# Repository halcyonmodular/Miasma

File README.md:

# Miasma
Miasma : Dual VCO Module Documentation

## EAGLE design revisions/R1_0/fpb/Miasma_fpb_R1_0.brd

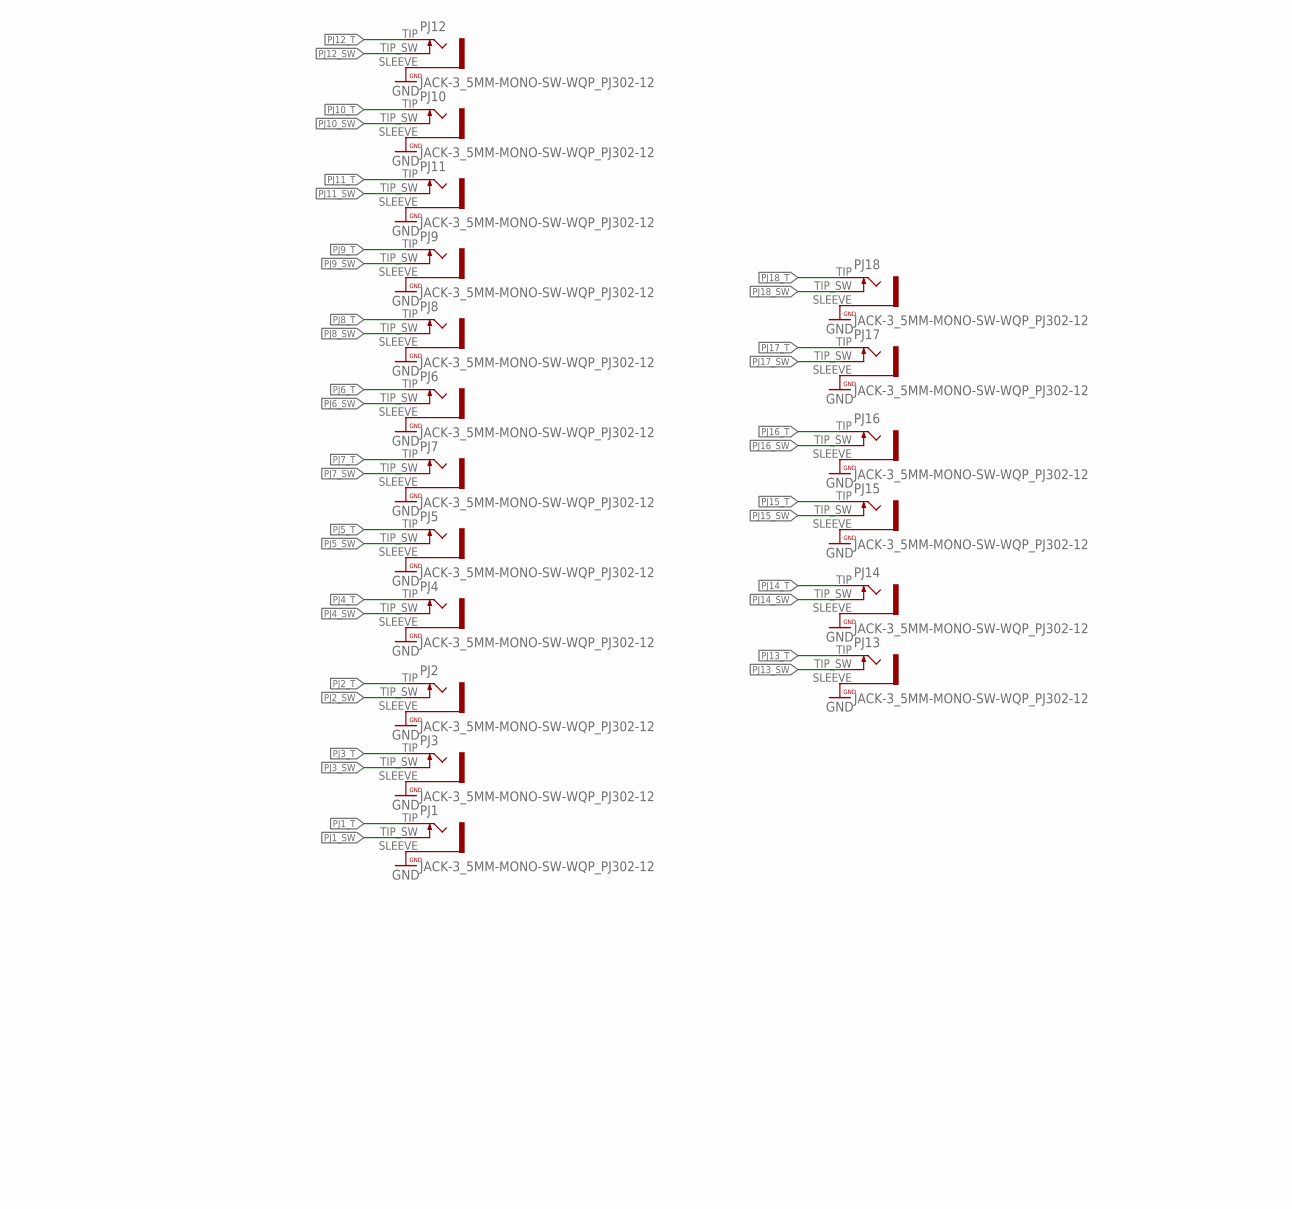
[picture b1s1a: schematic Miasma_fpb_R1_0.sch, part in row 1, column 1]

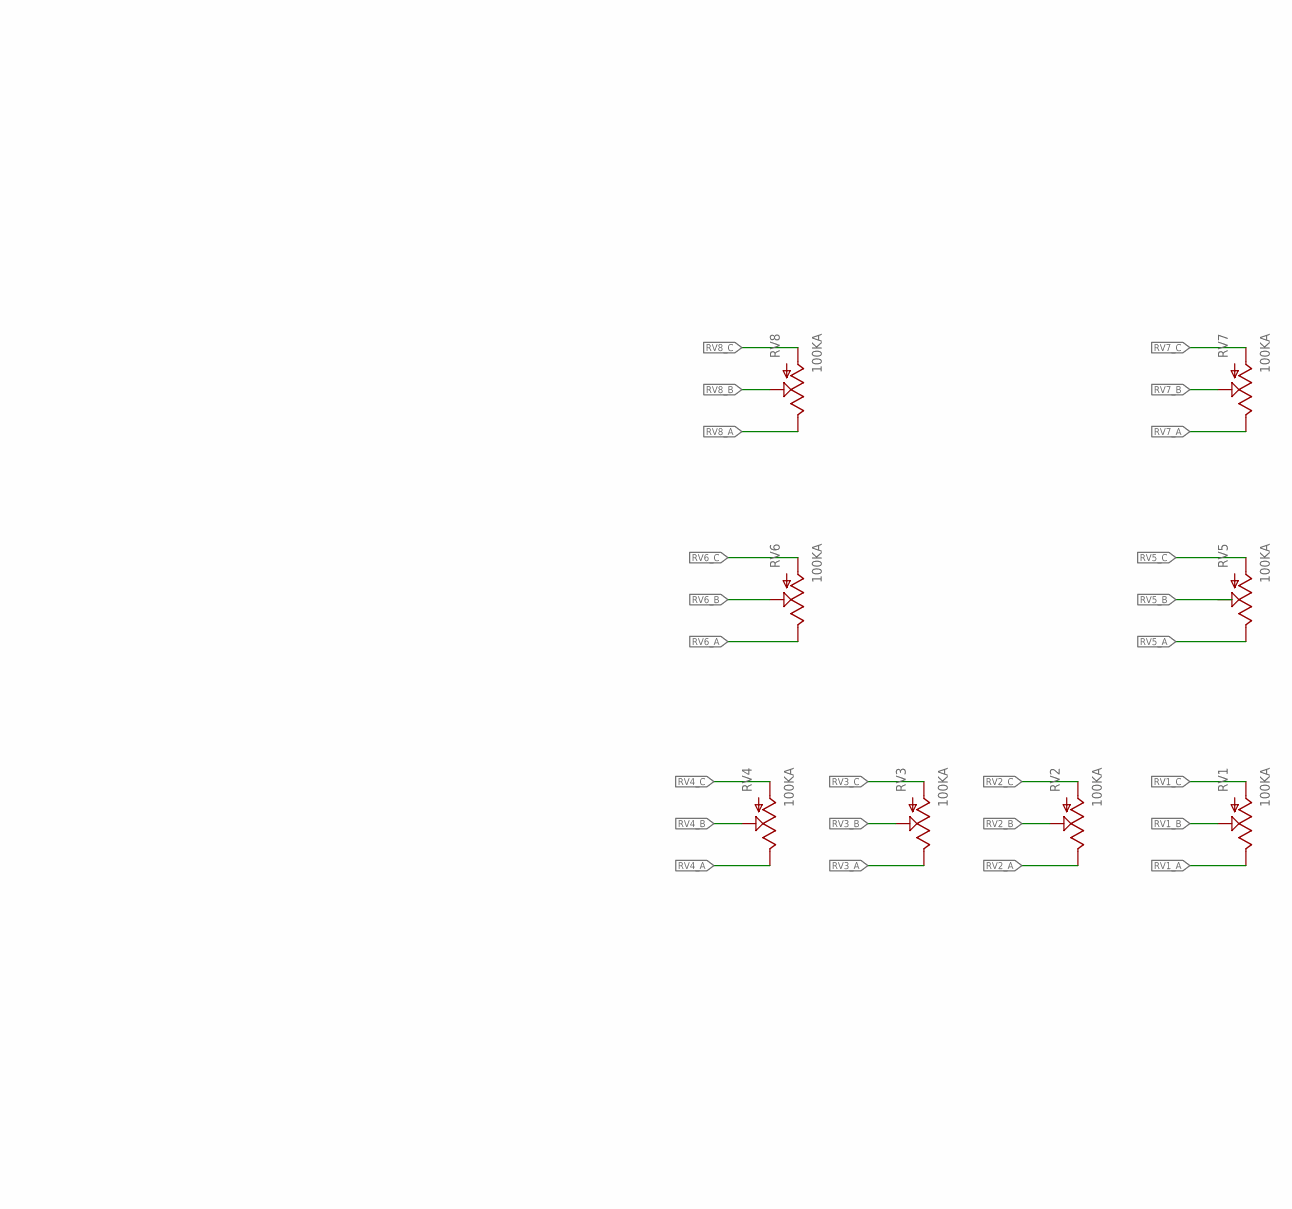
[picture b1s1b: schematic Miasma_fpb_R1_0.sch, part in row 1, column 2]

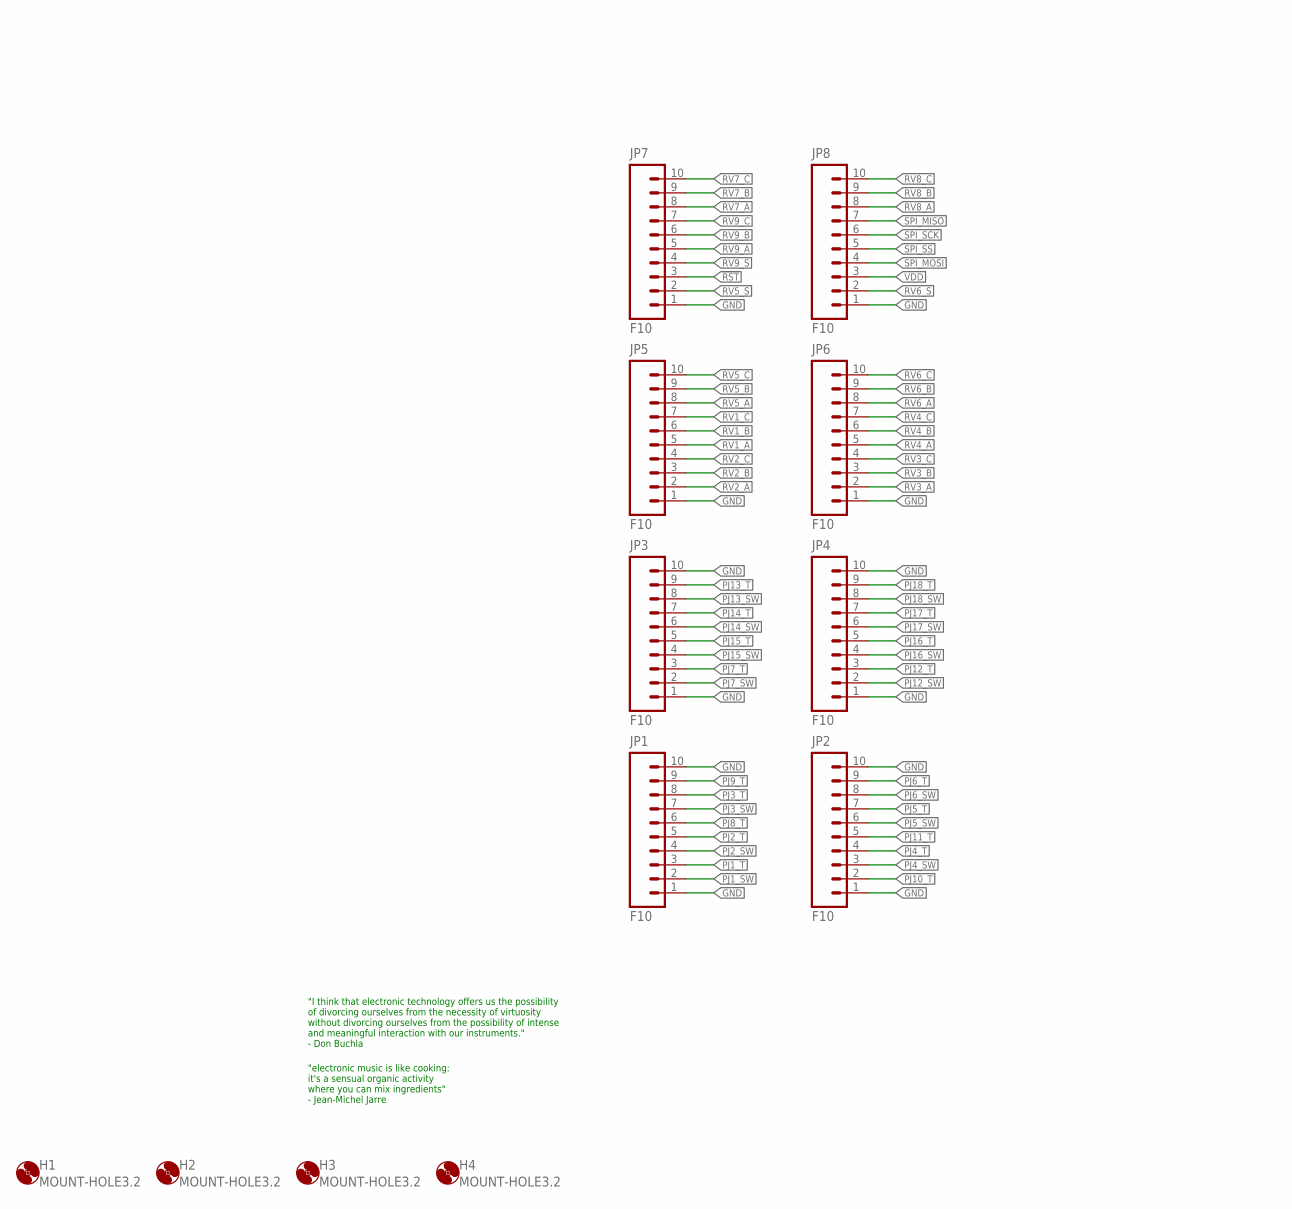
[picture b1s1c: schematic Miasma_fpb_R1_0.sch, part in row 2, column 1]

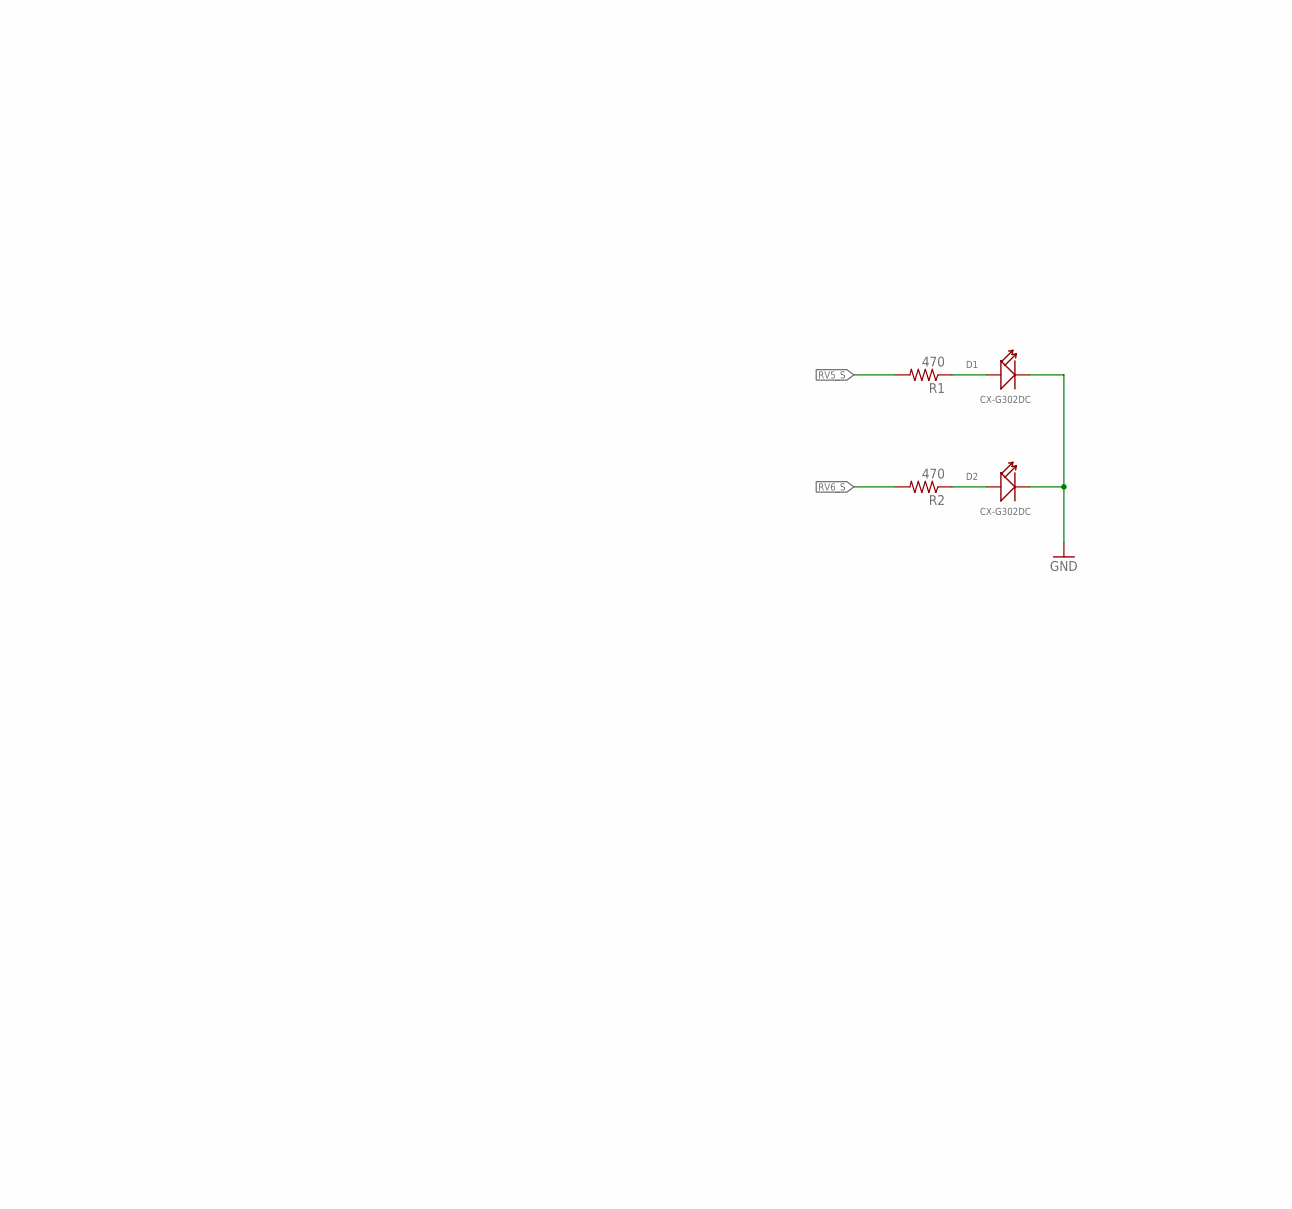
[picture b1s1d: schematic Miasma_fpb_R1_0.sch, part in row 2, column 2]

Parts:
D1, D2: CX-G302DC; LED2-2.54-D3.0MM
H1, H2, H3, H4: MOUNT-HOLE3.2; 3,2
JP1, JP2, JP3, JP4, JP5, JP6, JP7, JP8: F10; 1X10_OCTO
PJ1, PJ2, PJ3, PJ4, PJ5, PJ6, PJ7, PJ8, PJ9, PJ10, PJ11, PJ12, PJ13, PJ14, PJ15, PJ16, PJ17, PJ18: JACK-3_5MM-MONO-SW-WQP_PJ302-12; WQP_PJ301M-12
R1, R2: 470; R0603
RV1, RV2, RV3, RV4, RV5, RV6, RV7, RV8: 100KA; ALPS_POT

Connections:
!RST: JP7.3
GND: D1.K (-), D2.K (-), JP1.1, JP1.10, JP2.1, JP2.10, JP3.1, JP3.10, JP4.1, JP4.10, JP5.1, JP6.1, JP7.1, JP8.1, PJ1.SLEEVE, PJ2.SLEEVE, PJ3.SLEEVE, PJ4.SLEEVE, PJ5.SLEEVE, PJ6.SLEEVE, PJ7.SLEEVE, PJ8.SLEEVE, PJ9.SLEEVE, PJ10.SLEEVE, PJ11.SLEEVE, PJ12.SLEEVE, PJ13.SLEEVE, PJ14.SLEEVE, PJ15.SLEEVE, PJ16.SLEEVE, PJ17.SLEEVE, PJ18.SLEEVE
unnamed: D1.A (+), R1.1
unnamed: D2.A (+), R2.1
PJ1_SW: JP1.2, PJ1.TIP_SW
PJ1_T: JP1.3, PJ1.TIP
PJ2_SW: JP1.4, PJ2.TIP_SW
PJ2_T: JP1.5, PJ2.TIP
PJ3_SW: JP1.7, PJ3.TIP_SW
PJ3_T: JP1.8, PJ3.TIP
PJ4_SW: JP2.3, PJ4.TIP_SW
PJ4_T: JP2.4, PJ4.TIP
PJ5_SW: JP2.6, PJ5.TIP_SW
PJ5_T: JP2.7, PJ5.TIP
PJ6_SW: JP2.8, PJ6.TIP_SW
PJ6_T: JP2.9, PJ6.TIP
PJ7_SW: JP3.2, PJ7.TIP_SW
PJ7_T: JP3.3, PJ7.TIP
PJ8_SW: PJ8.TIP_SW
PJ8_T: JP1.6, PJ8.TIP
PJ9_SW: PJ9.TIP_SW
PJ9_T: JP1.9, PJ9.TIP
PJ10_SW: PJ10.TIP_SW
PJ10_T: JP2.2, PJ10.TIP
PJ11_SW: PJ11.TIP_SW
PJ11_T: JP2.5, PJ11.TIP
PJ12_SW: JP4.2, PJ12.TIP_SW
PJ12_T: JP4.3, PJ12.TIP
PJ13_SW: JP3.8, PJ13.TIP_SW
PJ13_T: JP3.9, PJ13.TIP
PJ14_SW: JP3.6, PJ14.TIP_SW
PJ14_T: JP3.7, PJ14.TIP
PJ15_SW: JP3.4, PJ15.TIP_SW
PJ15_T: JP3.5, PJ15.TIP
PJ16_SW: JP4.4, PJ16.TIP_SW
PJ16_T: JP4.5, PJ16.TIP
PJ17_SW: JP4.6, PJ17.TIP_SW
PJ17_T: JP4.7, PJ17.TIP
PJ18_SW: JP4.8, PJ18.TIP_SW
PJ18_T: JP4.9, PJ18.TIP
RV1_A: JP5.5, RV1.P$1 (3)
RV1_B: JP5.6, RV1.P$2 (2)
RV1_C: JP5.7, RV1.P$3 (1)
RV2_A: JP5.2, RV2.P$1 (3)
RV2_B: JP5.3, RV2.P$2 (2)
RV2_C: JP5.4, RV2.P$3 (1)
RV3_A: JP6.2, RV3.P$1 (3)
RV3_B: JP6.3, RV3.P$2 (2)
RV3_C: JP6.4, RV3.P$3 (1)
RV4_A: JP6.5, RV4.P$1 (3)
RV4_B: JP6.6, RV4.P$2 (2)
RV4_C: JP6.7, RV4.P$3 (1)
RV5_A: JP5.8, RV5.P$1 (3)
RV5_B: JP5.9, RV5.P$2 (2)
RV5_C: JP5.10, RV5.P$3 (1)
RV5_S: JP7.2, R1.2
RV6_A: JP6.8, RV6.P$1 (3)
RV6_B: JP6.9, RV6.P$2 (2)
RV6_C: JP6.10, RV6.P$3 (1)
RV6_S: JP8.2, R2.2
RV7_A: JP7.8, RV7.P$1 (3)
RV7_B: JP7.9, RV7.P$2 (2)
RV7_C: JP7.10, RV7.P$3 (1)
RV8_A: JP8.8, RV8.P$1 (3)
RV8_B: JP8.9, RV8.P$2 (2)
RV8_C: JP8.10, RV8.P$3 (1)
RV9_A: JP7.5
RV9_B: JP7.6
RV9_C: JP7.7
RV9_S: JP7.4
SPI_MISO: JP8.7
SPI_MOSI: JP8.4
SPI_SCK: JP8.6
SPI_SS: JP8.5
VDD: JP8.3

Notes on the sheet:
"electronic music is like cooking: it's a sensual organic activity where you can mix ingredients" - Jean-Michel Jarre
"I think that electronic technology offers us the possibility of divorcing ourselves from the necessity of virtuosity without divorcing ourselves from the possibility of intense and meaningful interaction with our instruments." - Don Buchla

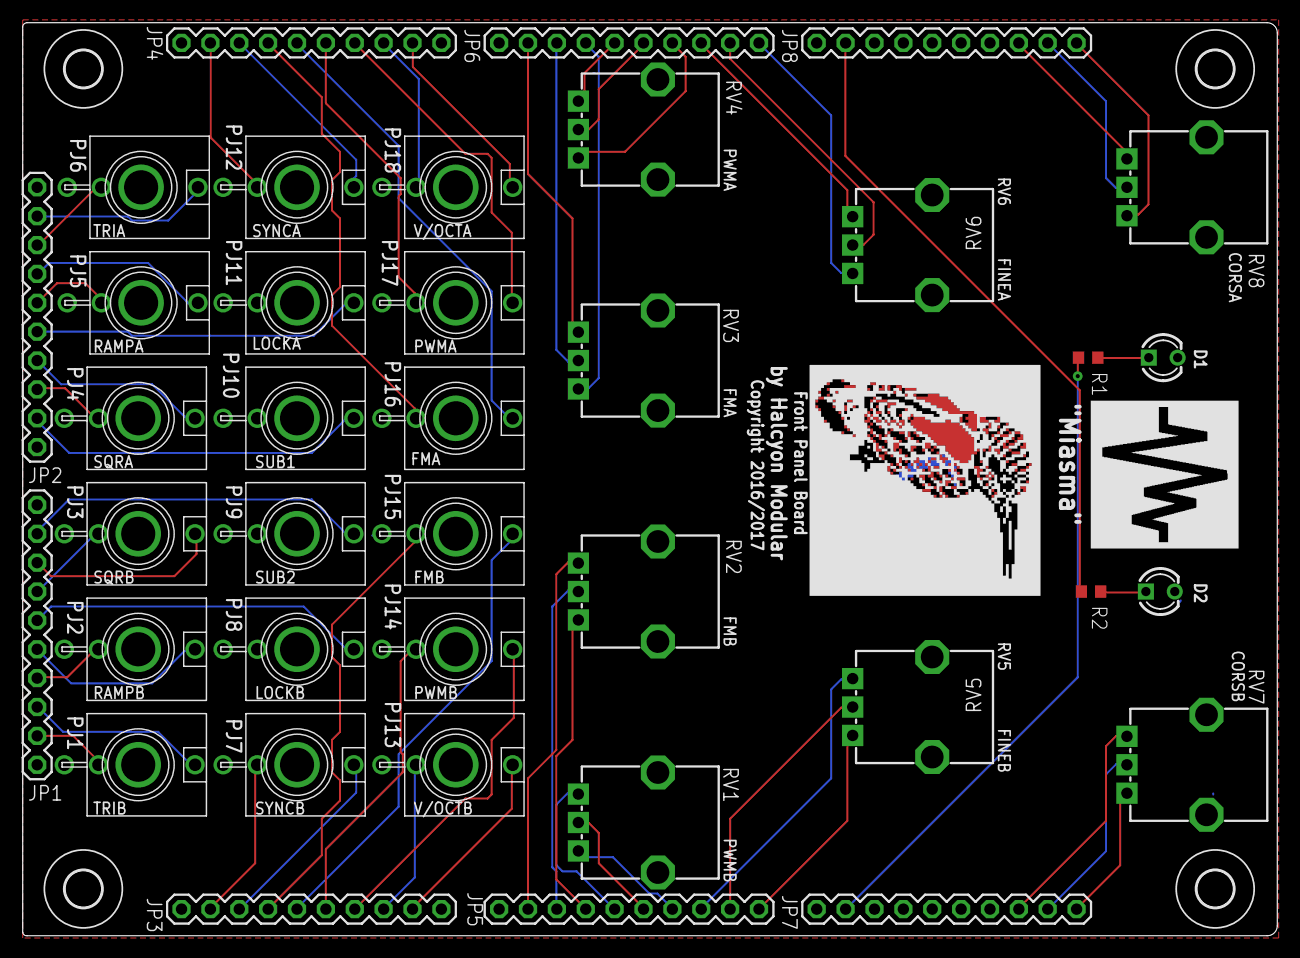
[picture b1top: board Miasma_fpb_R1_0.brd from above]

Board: 2 copper layers, 110.4 x 80.3 mm, 45 parts (1 on the bottom side), 61 nets.

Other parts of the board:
U$1: KINGFISH9_MED
U$3: KINGFISH_MED_TOPT
U$9: WAVE_MED

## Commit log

2017-07-14 initial checkin
2017-07-26 add front panel template
2017-07-30 Revision 1.0 updates
2017-08-24 update BOM

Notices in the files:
revisions/R1_0/fpb/Miasma_fpb_R1_0.brd:
Copyright 2016/2017
parts and their libraries:
PatternAgents-Beautify: License : http://creativecommons.org/licenses/by-sa/3.0
(Creative Commons 3.0)
